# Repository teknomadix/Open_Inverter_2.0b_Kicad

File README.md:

# OPEN INVERTER V2.0b (Kicad)

---

## This is a revision of [Johannes Hübner](https://johanneshuebner.com)'s OpenInverter 2.0 board.

---
The original board was designed in Eagle 6.0.  Since that is a bit antiquated now, and not open-source, it seemed important to have a more modern version of the hardware design files that are drawn up with an Open-source tool-set.

`KiCad ^5.0` is required to view / modify these source files.  

This hardware is released under the [CREATIVE COMMONS ATTRIBUTION - SHARE ALIKE 4.0 INTERNATIONAL LICENSE](https://creativecommons.org/licenses/by-sa/4.0/)

Please see the LICENSE file for more information about copying and distribution

BOM 
---
https://octopart.com/bom-tool/NGFoe5pd

If you want to purchase an assembly kit you can find them here:

[**WORLD**: @ https://openinverter.org](https://openinverter.org)

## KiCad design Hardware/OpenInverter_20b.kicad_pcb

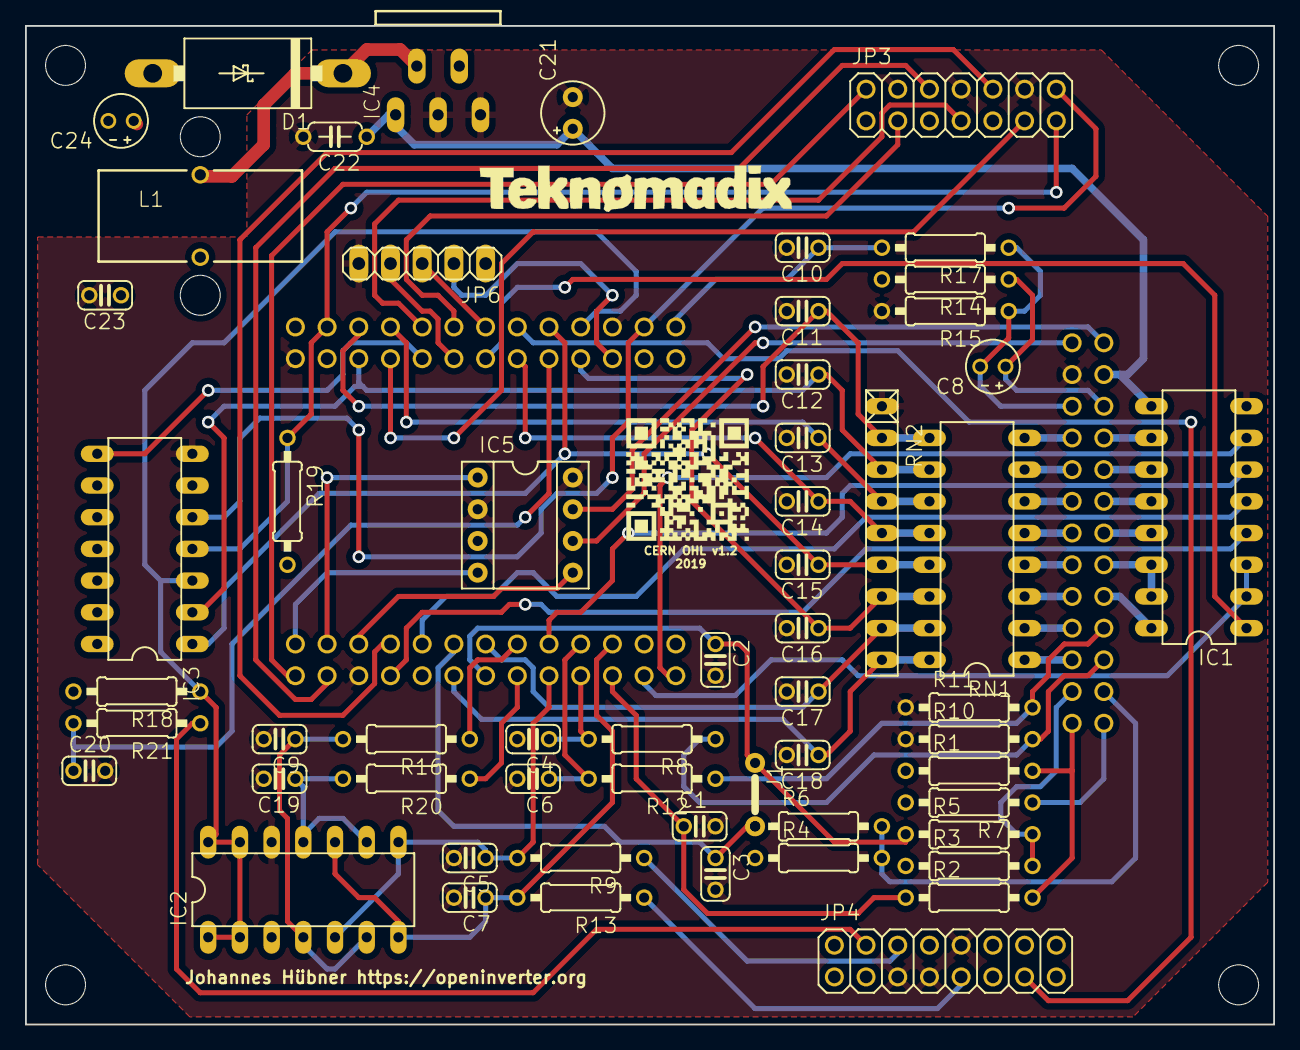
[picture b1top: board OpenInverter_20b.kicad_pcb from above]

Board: 4 copper layers, 100.0 x 80.0 mm, 67 parts (0 on the bottom side), 75 nets.

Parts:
@HOLE0, @HOLE1, @HOLE2, @HOLE3, @HOLE4, @HOLE5: (no value)
C1, C2, C3, C5, C7: 1nF; C025-024X044
C4, C6, C9, C10, C11, C12, C13, C14, C15, C16, C17, C18, C19, C20, C23: 1µ; C025-024X044
C8: 10µ; E2-4
C21: 680µ; E2,5-5
C22: 0.1µ; C050-024X044
C24: 220µ; E2-4
D1: SB540E-G; DO201T15
IC1: ULN2003AN; DIL16
IC2: LM2901; DIL14
IC3: 7430N; DIL14
IC4: LM2596; TO220-51
IC5: MCP2562P; DIL08
J1: J5MM; 05
JP1, JP2, JP5: 2X13
JP3: 2X07
JP4: 2X08
JP6: 1X05
L1: 50µH; TJ3-U1
R1, R3, R4: 500; 0207_10
R2, R5, R6, R8, R10, R11, R12, R16, R17, R18, R19, R20, R21: 10k; 0207_10
R7: 120R; 0207_10
R9, R13: 3.3k; 0207_10
R14, R15: 500R; 0207_10
RN1: 4.7k; DIL16
RN2: 1.2k; RN-9

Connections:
3.3V_IN: JP2.5, JP6.2
3.3V_OUT: IC5.5, JP1.5
12V: C21.+, C22.1, IC1.9, IC4.1, JP5.24
CANH: IC5.7, JP5.26
CANL: IC5.6, JP5.25
GND: C1.2, C2.2, C3.2, C4.2, C5.2, C6.2, C7.2, C9.2, C10.2, C11.2, C12.2, C13.2, C14.2, C15.2, C16.2, C17.2, C18.2, C19.2, C20.2, C21.-, C22.2, C23.2, C24.-, D1.A, IC1.8, IC2.12, IC3.7, IC4.3, IC4.5, IC5.2, IC5.8, JP1.6, JP2.6, JP2.25, JP3.4, JP3.8, JP3.12, JP4.5, JP4.7, JP4.10, JP5.23, JP6.5, R10.1, R11.1, R15.2, RN2.1
I_L1: JP4.6, R9.1
I_L2: JP4.9, R13.1
unnamed: JP5.2, R7.1
unnamed: JP5.3, R3.2, R5.2
unnamed: JP5.1, R1.2, R2.2
unnamed: C19.1, IC2.9, IC2.11, R20.2
unnamed: JP5.4, R4.2, R6.2
unnamed: C8.+, JP5.22, R14.1
unnamed: D1.C, IC4.2, L1.1
unnamed: C9.1, IC2.4, IC2.6, R16.2
unnamed: C8.-, JP5.21, R15.1, R17.1
OUT_BRAKE: IC1.16, JP5.10
OUT_DCSW: IC1.14, IC1.15, JP5.12
OUT_ERR: IC1.13, JP5.14
OUT_OVTMP: IC1.12, JP5.16
OUT_PRE: IC1.10, JP5.20
OUT_TEMP: IC1.11, JP5.18
PA0/ADC0: IC3.5, JP2.4, JP3.14
PA1/TIM2_CH2: IC2.1, IC2.2, IC2.13, IC2.14, IC3.3, JP2.8, R18.1
PA2/ADC2: C16.1, JP2.7, RN1.14, RN2.7
PA3/ADC3: C15.1, IC3.1, JP2.10, RN1.13, RN2.6
PA4/ADC4: C14.1, JP2.11, RN1.12, RN2.5
PA5/ADC5: C5.1, IC2.5, IC2.8, JP1.18, R9.2
PA6/TIM3_CH1: C2.1, J1.1, JP1.14, R5.1
PA7/TIM3_CH2: C1.1, JP1.22, R2.1
PA8/TIM1_CH1: JP1.2, JP3.2
PA9/USART1_TX/TIM1_CH2: JP1.4, JP3.6
PA10/USART1_RX/TIM1_CH3: JP1.7, JP3.10
PA11/CANRX: IC5.4, JP1.1
PA12/CANTX: IC5.1, JP1.3
PB0/ADC8: C7.1, IC2.7, IC2.10, JP1.21, R13.2
PB1/ADC9: IC1.7, JP1.26
PB5: C18.1, JP1.12, RN1.16, RN2.9
PB6/TIM4_CH1: C17.1, JP1.13, RN1.15, RN2.8
PB7/TIM4_CH2: JP1.15, R16.1
PB8/TIM4_CH3: JP1.16, R20.1
PB9/TIM4_CH4: IC1.6, JP1.17
PB10/USART3_TX: JP2.14, JP6.3
PB11/USART3_RX: JP2.15, JP6.4
PB12/TIM1_BKIN: IC3.8, JP2.17
PC0/ADC10: C6.1, JP1.19, R12.2
PC1/ADC11: C4.1, JP1.20, R8.2
PC2/ADC12: C10.1, JP2.2, R17.2
PC3/ADC13: C20.1, JP2.9, R21.2
PC4/ADC14: JP2.12, JP4.13
PC5/ADC15: IC1.1, JP2.13
PC6: C13.1, JP2.20, RN1.11, RN2.4
PC7: C12.1, IC3.2, JP2.21, RN1.10, RN2.3
PC8: C11.1, JP2.22, RN1.9, RN2.2
PC9: IC3.4, JP2.24, JP3.13, R19.1
PC10: IC1.4, JP1.8
PC11: IC1.5, JP1.9
PC13: IC1.2, IC1.3, JP1.24
PD2/TIM3_ETR: C3.1, J1.2, JP1.11, R6.1
SIG_BMS: JP5.19, RN1.8
SIG_BRAKE: JP5.9, RN1.3
SIG_CRUISE: JP5.5, RN1.1
SIG_EMCYSTOP: JP5.17, RN1.7
SIG_FORWARD: JP5.13, RN1.5
SIG_MPROT: JP5.11, RN1.4
SIG_REVERSE: JP5.15, RN1.6
SIG_START: JP5.7, RN1.2
TIM1_CH1N: JP2.16, JP3.3
TIM1_CH2N: JP2.18, JP3.7
TIM1_CH3N: JP2.19, JP3.11
UDC: JP4.4, R21.1
VCC: C23.1, C24.+, IC2.3, IC3.6, IC3.11, IC3.12, IC3.14, IC4.4, IC5.3, JP2.26, JP3.1, JP3.5, JP3.9, JP4.8, JP4.11, JP4.12, JP6.1, L1.2, R1.1, R3.1, R4.1, R7.2, R14.2, R18.2, R19.2
X: JP5.6, R8.1, R10.2
Y: JP5.8, R11.2, R12.1

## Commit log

2019-07-30 LICENSE-CC-BY-SA-4.0
2019-07-30 fix link

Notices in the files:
Hardware/OpenInverter_20b.kicad_pcb:
CERN OHL v1.2
